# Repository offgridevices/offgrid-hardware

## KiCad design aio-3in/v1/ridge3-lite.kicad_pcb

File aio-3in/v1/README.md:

# Ridge 3 Lite — v1

**One board that does it all:** the flight controller and the 4-in-1 ESC of a
3-inch quad on a single 38 × 38 mm board, for Project Cheap Drone Phase 1. A
battery lead and four motors connect to it, and it flies on stock Betaflight.
It has no FPV parts: no OSD, no video transmitter, no camera connector.

It replaces the GEPRC TAKER G4 AIO that Phase 1 flew. It uses the same
25.5 mm mounting pattern, and Betaflight's own TAKERG4AIO target runs on it
pin for pin.

> **Status: design complete, not yet built.** The board is fully routed
> (`ridge3-lite.kicad_pcb`): KiCad 10 DRC 0 errors, 0 warnings, 0
> unconnected, every fab gate and all 100 checks in `VERIFICATION.md` pass,
> and Gerbers, BOM, CPL and renders are in `production/` and `images/`.
> Nothing has been measured on hardware: build a few and go through
> bring-up before a volume order.

| | |
|---|---|
| Size | 38 × 38 mm, 3 mm corner radius, 25.5 mm M2 holes for soft-mount grommets |
| Battery | 2–4S LiPo, 4S HV (17.4 V) included; XT30 lead on solder pads |
| Motors | 4 × brushless, up to 15 A each continuous, 25 A peak (per-motor current limit) |
| Flight controller | STM32G473CEU6, ICM-42688-P gyro (BMI270 as second source), Betaflight |
| ESCs | 4 × STM32G071 + TI DRV8300D + 6 × Toshiba TPN2R304PL (40 V, 2.3 mΩ), AM32 |
| Power | 5 V 0.6 A BEC (TI LMR36506, 70 V input), 3.3 V for the FC and the ESCs, 11 V gate drive |
| Sensing | battery voltage and current to Betaflight; per-motor current and voltage to each ESC |
| PCB | 8 layers, 1.6 mm, 1 oz copper on every layer, 0.09 mm track and gap, vias down to 0.37 / 0.15 mm, every via filled and capped |

---

## What's on the board

- **Flight controller (top centre).** The STM32G473 runs Betaflight. It has:
  - the gyro on SPI1;
  - an 8 MHz crystal;
  - USB-C with ESD protection;
  - a BOOT button;
  - status and power LEDs;
  - a buzzer switch.

  There is no blackbox flash; log to an OpenLager on UART1 if needed.
- **Four ESCs, one per edge (bottom).** Each motor channel is the same layout,
  turned 90° per edge. Each has:
  - its own STM32G071 running AM32 (stock GEN_64K_G071 target);
  - a DRV8300D gate driver with 22 Ω / 10 Ω gate resistors, chosen by
    simulation to keep the FETs inside 40 V;
  - six FETs;
  - a 0.5 mΩ Kelvin shunt with an INA186 amplifier, so the ESC limits each
    motor's current itself;
  - back-EMF sensing and battery-voltage sensing.
- **Power.**
  - A 70 V-rated buck makes 5 V for the receiver and the LDOs.
  - A 60 V-rated LDO makes the 11 V gate drive.
  - A 22 V TVS clamps spikes on the battery.
  - The board runs from USB alone for configuration: everything powers up
    except the motors.
- **Pads.**
  - Battery + and − at the rear edge.
  - Three motor pads at each edge.
  - The receiver (UART2, 5 V, G) at the front.
  - Aux (UART1, LED strip, buzzer) at the right.
  - USB-C at the left.
  - SWD test points for each ESC's first flash, plated through so a probe
    reaches them from either side.

## Ordering

JLCPCB or PCBWay, from `production/`:

- **8 layers, 1.6 mm, 1 oz copper on every layer.** Layers: F (parts, power) / In1
  ground plane / In2-In4 signals / In5 the channels' return pours / In6 battery plane / B
  (parts, power).
- **0.09 mm (3.5 mil) track and gap, vias down to 0.37 / 0.15 mm** (also 0.4 / 0.2 and 0.5 / 0.25 mm). Both are inside
  JLCPCB's multilayer capability, but they are its fine-line and small-via
  price tiers: expect them on the quote. The board needs them: 260 parts on
  38 mm leave no room for 0.1 mm rules. Going to 40 mm would not help (the
  congestion is round the flight controller in the middle, not at the edges).
- **Matte black solder mask, white silkscreen, ENIG.**
- **Via-in-pad: "Epoxy filled & capped" (POFV).** Every via is filled; on 6+
  layers JLCPCB does this at no extra charge.
- Assembly: upload the BOM and CPL from `production/`. All assembled parts
  are on both sides; JLCPCB's two-sided assembly.
- **Fit by hand after assembly:**
  - the XT30 battery lead on the battery pads;
  - the bulk capacitor across the same pads (`docs/bulk-capacitor.md`:
    2 × Rubycon 35PZK470M10X11, or 1 × Panasonic EEH-AZSV681UB);
  - the motor wires.

**Check before you pay:** the SMF22A-TP's cathode band must face pad 1 (battery
+) in JLCPCB's placement preview. MCC's library symbol does not mark it.

## Bring-up

Firmware and every setting are in `firmware/`, with a README that walks
through it. In short:

1. USB only: flash Betaflight. Use the stock TAKERG4AIO target, or this
   board's RIDGE3LITE build; both are in `firmware/betaflight/`. Then paste
   `cli-setup.txt`.
2. Still on USB: flash each ESC's AM32 bootloader and firmware once over SWD
   (`firmware/am32/flash_esc.sh`). Then set them in ESC-configurator through
   Betaflight passthrough (`esc-settings.md`).
3. Battery, props off:
   - check motor order and direction in Betaflight's Motors tab;
   - check that the gyro moves the right way. The IMU sits at 135°; see
     `firmware/gyro-orientation.md`.

## What was checked

Each check is a gate: the build stops if it fails. All of these pass now.

| Check | Result |
|---|---|
| Every part has a footprint and an LCSC number; every pin is on its footprint; no single-pin net | pass, 260 parts |
| Firmware pin map: FC against Betaflight TAKERG4AIO, all four ESCs against AM32 GEN_64K_G071 (`src/verify.py`) | pass, pin for pin |
| Gyro orientation against Betaflight's alignment maths | pass |
| Routed board, KiCad 10 DRC | 0 errors, 0 warnings, 0 unconnected |
| Every part in production (`docs/lifecycle.md`) | 45 parts checked; 2 swapped for active parts |
| Volume sourcing for 10,000 boards (`docs/sourcing-10k.md`) | second sources and factory lead times listed |

### Simulation (`sim/`)

Worst case: a 4S HV pack (17.4 V), XING2 1404 3800KV on 3" props
(15 A per motor sustained, 25 A stalled).

- **Half-bridge switching (ngspice, fitted FET model).**
  - Peak FET voltage is 29.7–32.2 V at 15 A and 39.4 V at 30 A with 4 nH of
    loop, against the FETs' 40 V. The 22 / 10 Ω gate resistors fixed a
    41–50 V overshoot found in the first draft.
  - The switch node slews at most 1.85 V/ns.
- **Battery spikes.**
  - 18.6 V worst with the bulk capacitor fitted; the TVS never conducts in
    normal use.
  - Unplugging the pack while the motors brake reaches 57 V. No TVS this
    size can absorb that: keep the lead soldered or the XT30 seated.
- **Gate supply, BEC, sense chains.** All within ratings at a 100 °C board.
  The current sense reads 20 mV/A per ESC and 12 mV/A total.
- **Thermal (finite-volume model of the routed eight-layer board; `sim/thermal/`).**
  Validated against Toshiba's published Rth(ch-a) to within 2 %.

### Heat: what the board can do on a hot day

The routed board as ordered (8 layers, 1 oz, bare, no heat sink), 50 °C air,
1000 W/m² of sun on the board, prop wash (`sim/thermal/`, `--case desert`):

| Flight | FET (limit 175) | ESC MCU (105) | Gyro (85) |
|---|---|---|---|
| Armed on the ground, still air | 74 °C | 79 °C | |
| Hover | 98 °C | 95 °C | **89 °C** |
| Cruise | 110 °C | 101 °C | |
| 8 punches of 3 s full throttle | 119 °C | 110 °C | |
| Full throttle, 60 s | 165 °C | **154 °C** | **120 °C** |
| Motor 1 stalled at 25 A for 2 s | **179 °C** | 102 °C | |

At 25 °C in the shade, hover is 67 / 64 / 57 °C and 60 s of full throttle is
130 / 119 / 88 °C.  With half the prop wash, 60 s of full throttle would reach
225 °C: on such a day the ESCs' temperature limit, not the copper, is what
keeps the board alive.  Channel 1 runs hottest: it sits by the battery pads,
where all 60 A enter.  Its FETs are 40 °C above channel 4's at full throttle.

**What this means.**
- In normal flying on a normal day nothing comes near a limit.
- On a 50 °C day in direct sun the board will not burn out. Each ESC's
  temperature limit (AM32, 100 °C on its own chip) throttles that motor back
  first. The ESC chip tracks its FETs closely (154 against 165 °C at the end
  of the 60 s run), so the cut-back starts with the FETs near 110 °C, far
  under their 175 °C. Sustained full throttle on such a day is therefore
  throttled (by about two thirds on the placed board's estimate,
  `sim/thermal/results-size-cooling.md`), more if the prop wash is weak.
- A jammed prop is cut by AM32's stuck-rotor protection; the 2 s stall above
  is the case where it fails to act, and stays within 4 °C of the FET rating.
- Short punches are fine.
- Under those conditions the gyro runs slightly over its rated 85 °C even at
  hover, and Betaflight's gyro drifts with temperature.

**Fixes, in order of value:**
1. Keep the sun off the board. A frame top plate or a canopy over the stack
   removes the 1000 W/m² of sun, the largest single input at hover.
2. A finned aluminium top sink (9.6 g, 4 mm fins) takes 25–35 °C off at full
   throttle.

The full tables, with every cooling option, 35 against 38 mm and 1 against
2 oz, are in `sim/thermal/results-size-cooling.md`.

## Limits

- **Battery:** 2–4S. 5S and up exceed the FETs' 40 V rating under switching
  spikes.
- **The pack must stay connected while the motors spin** (see the 57 V
  case above).
- **Motors:** keep each ESC's current limit at 26 A or lower (`esc-settings.md`).
- **Bulk capacitor:** it must be fitted. Without it the battery ripple is
  2–7 V p-p and a hot plug rings to 26 V.

## Files

```
README.md                  this file
firmware/                  Betaflight and AM32 hex files, settings, flashing scripts
docs/                      lifecycle, 10k sourcing, bulk capacitor, gyro second source
sim/                       circuit simulations (ngspice) and the thermal model
src/                       the generator: circuit, footprints, placement, power copper, routing, checks
tools/                     the pinned KiCad 10 toolchain (Docker) and helpers
```

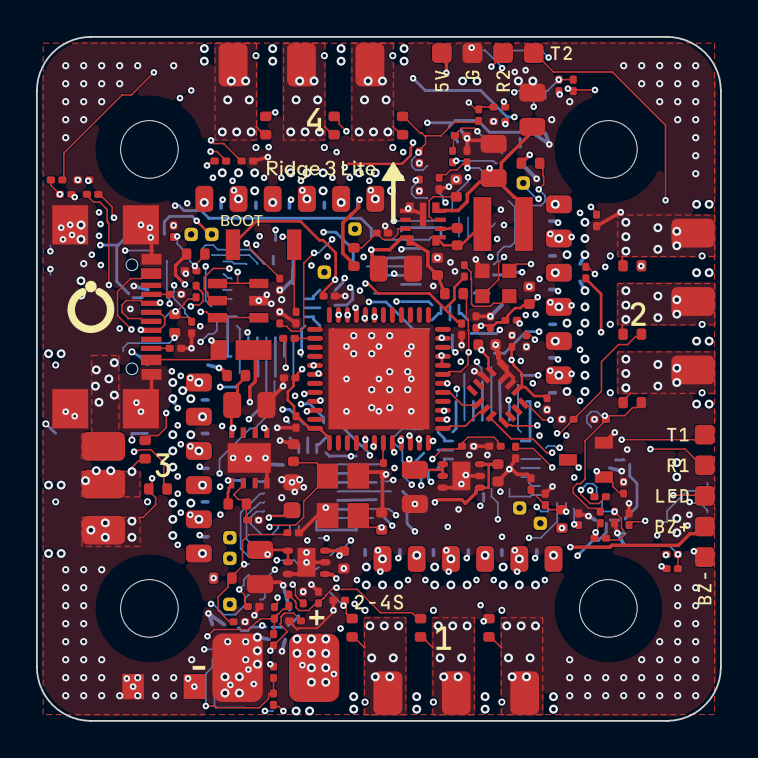
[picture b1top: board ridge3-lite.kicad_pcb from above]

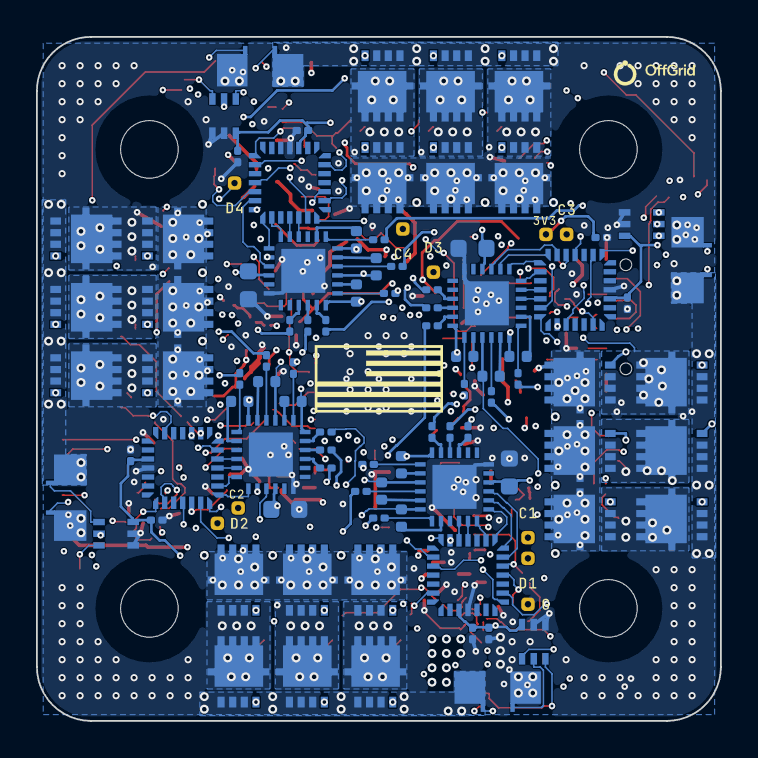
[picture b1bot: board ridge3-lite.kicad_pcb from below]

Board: 8 copper layers, 38.0 x 38.0 mm, 260 parts (88 on the bottom side), 188 nets.

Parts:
C1, C8, C10, C11, C104, C106, C108, C204, C206, C208, C304, C306, C308, C404, C406, C408: 4.7uF; C_0805_2012Metric
C2, C3: 100nF; C_0402_1005Metric_L
C4, C7, C9, C103, C105, C107, C203, C205, C207, C303, C305, C307, C403, C405, C407: 1uF; C_0402_1005Metric_L
C5, C6: 22uF; C_0805_2012Metric
C12, C102, C202, C302, C402: 10uF; C_0603_1608Metric_L
C13, C14, C15, C16, C17, C18, C19, C22, C26, C27, C101, C109, C110, C111, C201, C209, C210, C211, C301, C309, C310, C311, C401, C409, C410, C411: 100nF; C_0201_0603Metric_L
C20: 1uF; C_0201_0603Metric_L
C21, C25: 4.7uF; C_0402_1005Metric_L
C23, C24: 12pF; C_0402_1005Metric_L
D_TVS: SMF22A; SOD-123FL_L2.8-W1.9-LS3.7-RD
D_USB: SS1040HE; SOD-323HE_L2.0-W1.4-LS2.5-RD
H1, H2, H3, H4: HOLE; MOUNT_M2
J_USB: USB-C; USB-C-SMD_TYPE-C-16P-USB4110-GF-A
LED_PWR: red; LED0603-RD
LED_STAT: blue; LED0603-RD
L_BEC: 10uH; IND-SMD_L3.0-W3.0_SWPA3010S
P_5V: PAD_SIG
P_BAT+: PAD_BAT
P_BAT-: PAD_BAT
P_BZ+: PAD_SIG
P_BZ-: PAD_SIG
P_G: PAD_SIG
P_LED: PAD_SIG
P_M1A, P_M1B, P_M1C, P_M2A, P_M2B, P_M2C, P_M3A, P_M3B, P_M3C, P_M4A, P_M4B, P_M4C: PAD_MOTOR
P_R1, P_R2: PAD_SIG
P_T1, P_T2: PAD_SIG
Q1AH, Q1AL, Q1BH, Q1BL, Q1CH, Q1CL, Q2AH, Q2AL, Q2BH, Q2BL, Q2CH, Q2CL, Q3AH, Q3AL, Q3BH, Q3BL, Q3CH, Q3CL, Q4AH, Q4AL, Q4BH, Q4BL, Q4CH, Q4CL: TPN2R304PL; TSON-8_L3.1-W3.1-P0.65-LS3.3-BL-EP
Q_BZ: AO3400A; SOT-23-3_L2.9-W1.3-P1.90-LS2.4-BR
R1, R119, R219, R319, R419: 100k; R_0402_1005Metric_L
R2: 27k; R_0201_0603Metric_L
R3: 10R; R_0402_1005Metric_L
R4: 82k; R_0402_1005Metric_L
R5, R9, R16, R105, R110, R115, R118, R120, R205, R210, R215, R218, R220, R305, R310, R315, R318, R320, R405, R410, R415, R418, R420: 10k; R_0201_0603Metric_L
R6, R103, R108, R113, R203, R208, R213, R303, R308, R313, R403, R408, R413: 10k; R_0402_1005Metric_L
R7, R13, R117, R217, R317, R417: 1k; R_0201_0603Metric_L
R8: 62k; R_0201_0603Metric_L
R10, R102, R107, R112, R202, R207, R212, R302, R307, R312, R402, R407, R412: 10R; R_0201_0603Metric_L
R11, R12: 5.1k; R_0201_0603Metric_L
R14: 330R; R_0201_0603Metric_L
R15: 100R; R_0201_0603Metric_L
R101, R106, R111, R201, R206, R211, R301, R306, R311, R401, R406, R411: 22R; R_0201_0603Metric_L
R104, R109, R114, R204, R209, R214, R304, R309, R314, R404, R409, R414: 2.2k; R_0201_0603Metric_L
R116, R216, R316, R416: 1.5k; R_0201_0603Metric_L
R_S1, R_S2, R_S3, R_S4: 0.5mOhm; RES-SMD_1206_HCS1206
SW_BOOT: BOOT; KEY-SMD_B3U-1000PM
TP_3V3: PAD_TP
TP_C1, TP_C2, TP_C3, TP_C4: PAD_TP
TP_D1, TP_D2, TP_D3, TP_D4: PAD_TP
TP_GND: PAD_TP
U_A1, U_A2, U_A3, U_A4: INA186A3; SC-70-6_L2.0-W1.3-P0.65-LS2.1-BL-1
U_BEC: LMR36506R5; VQFN-9_L2.1-W2.1-P0.50-TL
U_D1, U_D2, U_D3, U_D4: DRV8300DRGER; VQFN-24_L4.0-W4.0-P0.50-TL-EP2.5
U_E1, U_E2, U_E3, U_E4: STM32G071GBU6; UFQFPN-28_L4.0-W4.0-P0.50-BL
U_ESD: USBLC6-2SC6; SOT-23-6_L2.9-W1.6-P0.95-LS2.8-BL
U_FC: STM32G473CEU6; UFQFPN-48_L7.0-W7.0-P0.50-BL-EP5.6
U_GVDD: TPS7A1601; SON-8_L3.0-W3.0-P0.65-TL-EP
U_IMU: ICM-42688-P; LGA-14_L3.0-W2.5-P0.50-TL
U_LDO: TLV76733; WSON-6_L2.0-W2.0-P0.65-TL-EP
U_LDOE: TLV76733; WSON-6_L2.0-W2.0-P0.65-TL-EP
Y1: 8 MHz; CRYSTAL-SMD_4P-L3.2-W2.5-BL

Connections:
+3V3: C8.1, C15.1, C16.1, C17.1, C18.1, C19.1, C20.1, C21.1, R10.1, R13.1, R14.1, SW_BOOT.1, U_FC.1, U_FC.20, U_FC.21, U_FC.23, U_FC.35, U_FC.48, U_LDO.1, U_LDO.2
+3V3E: C10.1, C101.1, C109.1, C201.1, C209.1, C301.1, C309.1, C401.1, C409.1, TP_3V3.1, U_A1.3, U_A2.3, U_A3.3, U_A4.3, U_E1.3, U_E2.3, U_E3.3, U_E4.3, U_LDOE.1, U_LDOE.2
+3V3_GYRO: C25.1, C26.1, C27.1, R10.2, U_IMU.5, U_IMU.8
+5V: C5.1, C6.1, C7.1, C9.1, D_USB.1, L_BEC.2, P_5V.1, P_BZ+.1, U_BEC.8, U_LDO.4, U_LDO.6, U_LDOE.4, U_LDOE.6
ADC_VBAT: C13.1, R6.2, R7.1, U_FC.19
BEC_BOOT: C3.1, U_BEC.6
BEC_EN: R1.2, R2.1, U_BEC.3
BEC_SW: C3.2, L_BEC.1, U_BEC.5
BEC_VCC: C4.1, U_BEC.7
BEEPER: R15.1, U_FC.38
BEEPER_G: Q_BZ.1, R15.2, R16.1
BOOT0: R9.1, SW_BOOT.2, U_FC.46
BZ-: P_BZ-.1, Q_BZ.3
CUR: C14.1, R8.1, R118.2, R218.2, R318.2, R418.2, U_FC.18
GND: C1.2, C2.2, C4.2, C5.2, C6.2, C7.2, C8.2, C9.2, C10.2, C11.2, C12.2, C13.2, C14.2, C15.2, C16.2, C17.2, C18.2, C19.2, C20.2, C21.2, C22.2, C23.2, C24.2, C25.2, C26.2, C27.2, C101.2, C102.2, C109.2, C110.2, C111.2, C201.2, C202.2, C209.2, C210.2, C211.2, C301.2, C302.2, C309.2, C310.2, C311.2, C401.2, C402.2, C409.2, C410.2, C411.2, D_TVS.2, J_USB.8, J_USB.9, J_USB.10, J_USB.11, J_USB.A1B12, J_USB.B1A12, LED_PWR.1, P_BAT-.1, P_G.1, Q_BZ.2, R2.2, R5.2, R7.2, R8.2, R9.2, R11.2, R12.2, R16.2, R104.2, R109.2, R114.2, R117.2, R120.2, R204.2, R209.2, R214.2, R217.2, R220.2, R304.2, R309.2, R314.2, R317.2, R320.2, R404.2, R409.2, R414.2, R417.2, R420.2, R_S1.2, R_S2.2, R_S3.2, R_S4.2, TP_GND.1, U_A1.1, U_A1.2, U_A2.1, U_A2.2, U_A3.1, U_A3.2, U_A4.1, U_A4.2, U_BEC.1, U_BEC.9, U_D1.6, U_D1.25, U_D2.6, U_D2.25, U_D3.6, U_D3.25, U_D4.6, U_D4.25, U_E1.4, U_E2.4, U_E3.4, U_E4.4, U_ESD.2, U_FC.49, U_GVDD.4, U_GVDD.9, U_IMU.6, U_IMU.7, U_IMU.9, U_LDO.3, U_LDO.5, U_LDO.7, U_LDOE.3, U_LDOE.5, U_LDOE.7, Y1.2, Y1.4
GVDD: C12.1, C102.1, C202.1, C302.1, C402.1, R4.1, U_D1.4, U_D2.4, U_D3.4, U_D4.4, U_GVDD.1
GVDD_FB: R4.2, R5.1, U_GVDD.2
GVDD_IN: C11.1, R3.2, U_GVDD.5, U_GVDD.8
GYRO_CS: U_FC.17, U_IMU.12
GYRO_INT: U_FC.12, U_IMU.4
HSE_IN: C23.1, U_FC.5, Y1.1
HSE_OUT: C24.1, U_FC.6, Y1.3
LED0: LED_STAT.1, U_FC.45
LED0_A: LED_STAT.2, R14.2
LED_PWR_A: LED_PWR.2, R13.2
LED_STRIP: P_LED.1, U_FC.44
M1_A: C103.2, P_M1A.1, Q1AH.1, Q1AH.2, Q1AH.3, Q1AL.5, Q1AL.6, Q1AL.7, Q1AL.8, Q1AL.9, R103.1, U_D1.18
M1_B: C105.2, P_M1B.1, Q1BH.1, Q1BH.2, Q1BH.3, Q1BL.5, Q1BL.6, Q1BL.7, Q1BL.8, Q1BL.9, R108.1, U_D1.15
M1_BSTA: C103.1, U_D1.20
M1_BSTB: C105.1, U_D1.17
M1_BSTC: C107.1, U_D1.14
M1_C: C107.2, P_M1C.1, Q1CH.1, Q1CH.2, Q1CH.3, Q1CL.5, Q1CL.6, Q1CL.7, Q1CL.8, Q1CL.9, R113.1, U_D1.12
M1_CMP_A: R103.2, R104.1, R105.1, U_E1.27
M1_CMP_B: R108.2, R109.1, R110.1, U_E1.23
M1_CMP_C: R113.2, R114.1, R115.1, U_E1.8
M1_GHA: Q1AH.4, R101.2
M1_GHA_D: R101.1, U_D1.19
M1_GHB: Q1BH.4, R106.2
M1_GHB_D: R106.1, U_D1.16
M1_GHC: Q1CH.4, R111.2
M1_GHC_D: R111.1, U_D1.13
M1_GLA: Q1AL.4, R102.2
M1_GLA_D: R102.1, U_D1.11
M1_GLB: Q1BL.4, R107.2
M1_GLB_D: R107.1, U_D1.10
M1_GLC: Q1CL.4, R112.2
M1_GLC_D: R112.1, U_D1.9
M1_HA: U_D1.22, U_E1.19
M1_HB: U_D1.23, U_E1.18
M1_HC: U_D1.24, U_E1.16
M1_IOUT: R116.1, R118.1, U_A1.6
M1_ISENSE: C110.1, R116.2, R117.1, U_E1.11
M1_LA: U_D1.1, U_E1.15
M1_LB: U_D1.2, U_E1.14
M1_LC: U_D1.3, U_E1.13
M1_NEUTRAL: R105.2, R110.2, R115.2, U_E1.9
M1_SIG: U_E1.24, U_FC.8
M1_SNSN: R_S1.4, U_A1.5
M1_SNSP: R_S1.3, U_A1.4
M1_SRC: C104.2, C106.2, C108.2, Q1AL.1, Q1AL.2, Q1AL.3, Q1BL.1, Q1BL.2, Q1BL.3, Q1CL.1, Q1CL.2, Q1CL.3, R_S1.1
M1_SWCLK: TP_C1.1, U_E1.21
M1_SWDIO: TP_D1.1, U_E1.20
M1_VSENSE: C111.1, R119.2, R120.1, U_E1.12
M2_A: C203.2, P_M2A.1, Q2AH.1, Q2AH.2, Q2AH.3, Q2AL.5, Q2AL.6, Q2AL.7, Q2AL.8, Q2AL.9, R203.1, U_D2.18
M2_B: C205.2, P_M2B.1, Q2BH.1, Q2BH.2, Q2BH.3, Q2BL.5, Q2BL.6, Q2BL.7, Q2BL.8, Q2BL.9, R208.1, U_D2.15
M2_BSTA: C203.1, U_D2.20
M2_BSTB: C205.1, U_D2.17
M2_BSTC: C207.1, U_D2.14
M2_C: C207.2, P_M2C.1, Q2CH.1, Q2CH.2, Q2CH.3, Q2CL.5, Q2CL.6, Q2CL.7, Q2CL.8, Q2CL.9, R213.1, U_D2.12
M2_CMP_A: R203.2, R204.1, R205.1, U_E2.27
M2_CMP_B: R208.2, R209.1, R210.1, U_E2.23
M2_CMP_C: R213.2, R214.1, R215.1, U_E2.8
M2_GHA: Q2AH.4, R201.2
M2_GHA_D: R201.1, U_D2.19
M2_GHB: Q2BH.4, R206.2
M2_GHB_D: R206.1, U_D2.16
M2_GHC: Q2CH.4, R211.2
M2_GHC_D: R211.1, U_D2.13
M2_GLA: Q2AL.4, R202.2
M2_GLA_D: R202.1, U_D2.11
M2_GLB: Q2BL.4, R207.2
M2_GLB_D: R207.1, U_D2.10
M2_GLC: Q2CL.4, R212.2
M2_GLC_D: R212.1, U_D2.9
M2_HA: U_D2.22, U_E2.19
M2_HB: U_D2.23, U_E2.18
M2_HC: U_D2.24, U_E2.16
M2_IOUT: R216.1, R218.1, U_A2.6
M2_ISENSE: C210.1, R216.2, R217.1, U_E2.11
M2_LA: U_D2.1, U_E2.15
M2_LB: U_D2.2, U_E2.14
M2_LC: U_D2.3, U_E2.13
M2_NEUTRAL: R205.2, R210.2, R215.2, U_E2.9
M2_SIG: U_E2.24, U_FC.9
M2_SNSN: R_S2.4, U_A2.5
M2_SNSP: R_S2.3, U_A2.4
M2_SRC: C204.2, C206.2, C208.2, Q2AL.1, Q2AL.2, Q2AL.3, Q2BL.1, Q2BL.2, Q2BL.3, Q2CL.1, Q2CL.2, Q2CL.3, R_S2.1
M2_SWCLK: TP_C2.1, U_E2.21
M2_SWDIO: TP_D2.1, U_E2.20
M2_VSENSE: C211.1, R219.2, R220.1, U_E2.12
M3_A: C303.2, P_M3A.1, Q3AH.1, Q3AH.2, Q3AH.3, Q3AL.5, Q3AL.6, Q3AL.7, Q3AL.8, Q3AL.9, R303.1, U_D3.18
M3_B: C305.2, P_M3B.1, Q3BH.1, Q3BH.2, Q3BH.3, Q3BL.5, Q3BL.6, Q3BL.7, Q3BL.8, Q3BL.9, R308.1, U_D3.15
M3_BSTA: C303.1, U_D3.20
M3_BSTB: C305.1, U_D3.17
M3_BSTC: C307.1, U_D3.14
M3_C: C307.2, P_M3C.1, Q3CH.1, Q3CH.2, Q3CH.3, Q3CL.5, Q3CL.6, Q3CL.7, Q3CL.8, Q3CL.9, R313.1, U_D3.12
M3_CMP_A: R303.2, R304.1, R305.1, U_E3.27
M3_CMP_B: R308.2, R309.1, R310.1, U_E3.23
M3_CMP_C: R313.2, R314.1, R315.1, U_E3.8
M3_GHA: Q3AH.4, R301.2
M3_GHA_D: R301.1, U_D3.19
M3_GHB: Q3BH.4, R306.2
M3_GHB_D: R306.1, U_D3.16
M3_GHC: Q3CH.4, R311.2
M3_GHC_D: R311.1, U_D3.13
M3_GLA: Q3AL.4, R302.2
M3_GLA_D: R302.1, U_D3.11
M3_GLB: Q3BL.4, R307.2
M3_GLB_D: R307.1, U_D3.10
M3_GLC: Q3CL.4, R312.2
M3_GLC_D: R312.1, U_D3.9
M3_HA: U_D3.22, U_E3.19
M3_HB: U_D3.23, U_E3.18
M3_HC: U_D3.24, U_E3.16
M3_IOUT: R316.1, R318.1, U_A3.6
M3_ISENSE: C310.1, R316.2, R317.1, U_E3.11
M3_LA: U_D3.1, U_E3.15
M3_LB: U_D3.2, U_E3.14
M3_LC: U_D3.3, U_E3.13
M3_NEUTRAL: R305.2, R310.2, R315.2, U_E3.9
M3_SIG: U_E3.24, U_FC.10
M3_SNSN: R_S3.4, U_A3.5
M3_SNSP: R_S3.3, U_A3.4
M3_SRC: C304.2, C306.2, C308.2, Q3AL.1, Q3AL.2, Q3AL.3, Q3BL.1, Q3BL.2, Q3BL.3, Q3CL.1, Q3CL.2, Q3CL.3, R_S3.1
M3_SWCLK: TP_C3.1, U_E3.21
M3_SWDIO: TP_D3.1, U_E3.20
M3_VSENSE: C311.1, R319.2, R320.1, U_E3.12
M4_A: C403.2, P_M4A.1, Q4AH.1, Q4AH.2, Q4AH.3, Q4AL.5, Q4AL.6, Q4AL.7, Q4AL.8, Q4AL.9, R403.1, U_D4.18
M4_B: C405.2, P_M4B.1, Q4BH.1, Q4BH.2, Q4BH.3, Q4BL.5, Q4BL.6, Q4BL.7, Q4BL.8, Q4BL.9, R408.1, U_D4.15
M4_BSTA: C403.1, U_D4.20
M4_BSTB: C405.1, U_D4.17
M4_BSTC: C407.1, U_D4.14
M4_C: C407.2, P_M4C.1, Q4CH.1, Q4CH.2, Q4CH.3, Q4CL.5, Q4CL.6, Q4CL.7, Q4CL.8, Q4CL.9, R413.1, U_D4.12
M4_CMP_A: R403.2, R404.1, R405.1, U_E4.27
M4_CMP_B: R408.2, R409.1, R410.1, U_E4.23
M4_CMP_C: R413.2, R414.1, R415.1, U_E4.8
M4_GHA: Q4AH.4, R401.2
M4_GHA_D: R401.1, U_D4.19
M4_GHB: Q4BH.4, R406.2
M4_GHB_D: R406.1, U_D4.16
M4_GHC: Q4CH.4, R411.2
M4_GHC_D: R411.1, U_D4.13
M4_GLA: Q4AL.4, R402.2
M4_GLA_D: R402.1, U_D4.11
M4_GLB: Q4BL.4, R407.2
M4_GLB_D: R407.1, U_D4.10
M4_GLC: Q4CL.4, R412.2
M4_GLC_D: R412.1, U_D4.9
M4_HA: U_D4.22, U_E4.19
M4_HB: U_D4.23, U_E4.18
M4_HC: U_D4.24, U_E4.16
M4_IOUT: R416.1, R418.1, U_A4.6
M4_ISENSE: C410.1, R416.2, R417.1, U_E4.11
M4_LA: U_D4.1, U_E4.15
M4_LB: U_D4.2, U_E4.14
M4_LC: U_D4.3, U_E4.13
M4_NEUTRAL: R405.2, R410.2, R415.2, U_E4.9
M4_SIG: U_E4.24, U_FC.11
M4_SNSN: R_S4.4, U_A4.5
M4_SNSP: R_S4.3, U_A4.4
M4_SRC: C404.2, C406.2, C408.2, Q4AL.1, Q4AL.2, Q4AL.3, Q4BL.1, Q4BL.2, Q4BL.3, Q4CL.1, Q4CL.2, Q4CL.3, R_S4.1
M4_SWCLK: TP_C4.1, U_E4.21
M4_SWDIO: TP_D4.1, U_E4.20
M4_VSENSE: C411.1, R419.2, R420.1, U_E4.12
NRST: C22.1, U_FC.7
SPI1_MISO: U_FC.14, U_IMU.1
SPI1_MOSI: U_FC.15, U_IMU.14
SPI1_SCK: U_FC.13, U_IMU.13
UART1_RX: P_R1.1, U_FC.32
UART1_TX: P_T1.1, U_FC.31
UART2_RX: P_R2.1, U_FC.42
UART2_TX: P_T2.1, U_FC.41
USB_CC1: J_USB.A5, R11.1
USB_CC2: J_USB.B5, R12.1
USB_DM: J_USB.A7, J_USB.B7, U_ESD.3, U_ESD.4, U_FC.33
USB_DP: J_USB.A6, J_USB.B6, U_ESD.1, U_ESD.6, U_FC.34
USB_VBUS: D_USB.2, J_USB.A4B9, J_USB.B4A9, U_ESD.5
VBAT: C1.1, C2.1, C104.1, C106.1, C108.1, C204.1, C206.1, C208.1, C304.1, C306.1, C308.1, C404.1, C406.1, C408.1, D_TVS.1, P_BAT+.1, Q1AH.5, Q1AH.6, Q1AH.7, Q1AH.8, Q1AH.9, Q1BH.5, Q1BH.6, Q1BH.7, Q1BH.8, Q1BH.9, Q1CH.5, Q1CH.6, Q1CH.7, Q1CH.8, Q1CH.9, Q2AH.5, Q2AH.6, Q2AH.7, Q2AH.8, Q2AH.9, Q2BH.5, Q2BH.6, Q2BH.7, Q2BH.8, Q2BH.9, Q2CH.5, Q2CH.6, Q2CH.7, Q2CH.8, Q2CH.9, Q3AH.5, Q3AH.6, Q3AH.7, Q3AH.8, Q3AH.9, Q3BH.5, Q3BH.6, Q3BH.7, Q3BH.8, Q3BH.9, Q3CH.5, Q3CH.6, Q3CH.7, Q3CH.8, Q3CH.9, Q4AH.5, Q4AH.6, Q4AH.7, Q4AH.8, Q4AH.9, Q4BH.5, Q4BH.6, Q4BH.7, Q4BH.8, Q4BH.9, Q4CH.5, Q4CH.6, Q4CH.7, Q4CH.8, Q4CH.9, R1.1, R3.1, R6.1, R119.1, R219.1, R319.1, R419.1, U_BEC.4

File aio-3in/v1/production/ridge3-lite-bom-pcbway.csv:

Item #,Designator,Qty,Manufacturer Part Number,Description,Value,Package/Footprint,Type,LCSC Part #,Side
1,"R5,R9,R16,R105,R110,R115,R118,R120,R205,R210,R215,R218,R220,R305,R310,R315,R318,R320,R405,R410,R415,R418,R420",23,RC0201FR-0710KL,Resistor 10k 1% 0201,10k,R_0201_0603Metric_L,SMD,C106225,Top
2,"R10,R102,R107,R112,R202,R207,R212,R302,R307,R312,R402,R407,R412",13,RC0201FR-0710RL,Resistor 10R 1% 0201,10R,R_0201_0603Metric_L,SMD,C106226,Bottom+Top
3,LED_PWR,1,LTST-C191KRKT,LED red 0603 (pad 1 cathode),red,LED0603-RD,SMD,C125099,Top
4,U_FC,1,STM32G473CEU6,"MCU Cortex-M4F 170 MHz, 512 KB flash, UFQFPN-48 (flight controller)",STM32G473CEU6,UFQFPN-48_L7.0-W7.0-P0.50-BL-EP5.6,SMD,C1342773,Top
5,"R7,R13,R117,R217,R317,R417",6,RC0201FR-071KL,Resistor 1k 1% 0201,1k,R_0201_0603Metric_L,SMD,C138165,Top
6,"R104,R109,R114,R204,R209,R214,R304,R309,R314,R404,R409,R414",12,RC0201FR-072K2L,Resistor 2.2k 1% 0201,2.2k,R_0201_0603Metric_L,SMD,C142018,Top
7,"C23,C24",2,0402CG120J500NT,Capacitor 12pF 50V C0G 0402,12pF,C_0402_1005Metric_L,SMD,C1547,Top
8,"R101,R106,R111,R201,R206,R211,R301,R306,R311,R401,R406,R411",12,RC0201FR-0722RL,Resistor 22R 1% 0201,22R,R_0201_0603Metric_L,SMD,C155743,Bottom
9,"C8,C10",2,CL21A475KAQNNNE,Capacitor 4.7uF 25V X5R 0805,4.7uF,C_0805_2012Metric,SMD,C1779,Top
10,U_IMU,1,ICM-42688-P,"6-axis IMU (gyro + accelerometer), SPI, LGA-14 2.5 x 3",ICM-42688-P,LGA-14_L3.0-W2.5-P0.50-TL,SMD,C1850418,Top
11,D_TVS,1,SMF22A-TP,"TVS 22 V stand-off, 35.5 V clamp at 5.6 A, 200 W, SOD-123FL",SMF22A,SOD-123FL_L2.8-W1.9-LS3.7-RD,SMD,C1974299,Top
12,"U_A1,U_A2,U_A3,U_A4",4,INA186A3IDCKR,"Current-sense amplifier 100 V/V, zero drift, SC-70-6",INA186A3,SC-70-6_L2.0-W1.3-P0.65-LS2.1-BL-1,SMD,C2058245,Bottom
13,Q_BZ,1,AO3400A,"N-MOSFET 30 V 5.7 A, SOT-23 (buzzer)",AO3400A,SOT-23-3_L2.9-W1.3-P1.90-LS2.4-BR,SMD,C20917,Top
14,SW_BOOT,1,B3U-1000P,Tactile switch 3 x 2.5 mm (DFU boot),BOOT,KEY-SMD_B3U-1000PM,SMD,C231329,Top
15,"C21,C25",2,CL05A475MP5NRNC,Capacitor 4.7uF 10V X5R 0402,4.7uF,C_0402_1005Metric_L,SMD,C23733,Top
16,R3,1,0402WGF100JTCE,Resistor 10R 1% 0402,10R,R_0402_1005Metric_L,SMD,C25077,Top
17,"R1,R119,R219,R319,R419",5,0402WGF1003TCE,Resistor 100k 1% 0402,100k,R_0402_1005Metric_L,SMD,C25741,Top
18,"R6,R103,R108,R113,R203,R208,R213,R303,R308,R313,R403,R408,R413",13,0402WGF1002TCE,Resistor 10k 1% 0402,10k,R_0402_1005Metric_L,SMD,C25744,Top
19,"R116,R216,R316,R416",4,0201WMF1501TEE,Resistor 1.5k 1% 0201,1.5k,R_0201_0603Metric_L,SMD,C270361,Top
20,R2,1,RC0201FR-0727KL,Resistor 27k 1% 0201,27k,R_0201_0603Metric_L,SMD,C273283,Top
21,"R11,R12",2,RC0201FR-075K1L,Resistor 5.1k 1% 0201,5.1k,R_0201_0603Metric_L,SMD,C274341,Top
22,R14,1,RC0201FR-07330RL,Resistor 330R 1% 0201,330R,R_0201_0603Metric_L,SMD,C274872,Top
23,D_USB,1,SS1040HEWS_R1_00001,"Schottky 40 V 1 A, SOD-323HE (USB OR-ing)",SS1040HE,SOD-323HE_L2.0-W1.4-LS2.5-RD,SMD,C282389,Top
24,"U_LDO,U_LDOE",2,TLV76733DRVR,"LDO 3.3 V 1 A, 16 V in, WSON-6 2 x 2",TLV76733,WSON-6_L2.0-W2.0-P0.65-TL-EP,SMD,C2848334,Top
25,U_BEC,1,LMR36506R5RPER,"Buck 4.2-65 V in, fixed 5 V 0.6 A, VQFN-HR-9 2 x 2 (BEC)",LMR36506R5,VQFN-9_L2.1-W2.1-P0.50-TL,SMD,C2866484,Top
26,U_GVDD,1,TPS7A1601DRBR,"LDO adjustable 100 mA, 60 V in, SON-8 3 x 3 (gate-drive supply)",TPS7A1601,SON-8_L3.0-W3.0-P0.65-TL-EP,SMD,C2867753,Top
27,R8,1,RC0201FR-0762KL,Resistor 62k 1% 0201,62k,R_0201_0603Metric_L,SMD,C295812,Top
28,"C2,C3",2,CL05B104KB54PNC,Capacitor 100nF 50V X7R 0402,100nF,C_0402_1005Metric_L,SMD,C307331,Top
29,"C13,C14,C15,C16,C17,C18,C19,C22,C26,C27,C101,C109,C110,C111,C201,C209,C210,C211,C301,C309,C310,C311,C401,C409,C410,C411",26,CL03A104KO3NNNC,Capacitor 100nF 16V X5R 0201,100nF,C_0201_0603Metric_L,SMD,C307380,Bottom+Top
30,"R_S1,R_S2,R_S3,R_S4",4,HCS1206FTL500,"Current shunt 0.5 mOhm 1 % 2 W, metal element, 1206",0.5mOhm,RES-SMD_1206_HCS1206,SMD,C346511,Bottom
31,"U_D1,U_D2,U_D3,U_D4",4,DRV8300DRGER,"100 V three-phase gate driver, bootstrap diodes, VQFN-24 4 x 4",DRV8300DRGER,VQFN-24_L4.0-W4.0-P0.50-TL-EP2.5,SMD,C3655801,Bottom
32,"C1,C11,C104,C106,C108,C204,C206,C208,C304,C306,C308,C404,C406,C408",14,GRM21BZ71H475KE15L,Capacitor 4.7uF 50V X7R 0805,4.7uF,C_0805_2012Metric,SMD,C437557,Top
33,L_BEC,1,SWPA3015S100MT,"Inductor 10 uH, 0.92 A sat, 0.77 A rms, 325 mOhm, shielded 3 x 3 x 1.5",10uH,IND-SMD_L3.0-W3.0_SWPA3010S,SMD,C45403,Top
34,R4,1,CRCW040282K0FKED,Resistor 82k 1% 0402,82k,R_0402_1005Metric_L,SMD,C482240,Top
35,J_USB,1,USB4110-GF-A,"USB-C receptacle, USB 2.0, 16 contacts, all-SMD shell",USB-C,USB-C-SMD_TYPE-C-16P-USB4110-GF-A,SMD,C5143397,Top
36,"C4,C7,C9,C103,C105,C107,C203,C205,C207,C303,C305,C307,C403,C405,C407",15,CL05A105KA5NQNC,Capacitor 1uF 25V X5R 0402,1uF,C_0402_1005Metric_L,SMD,C52923,Bottom+Top
37,"U_E1,U_E2,U_E3,U_E4",4,STM32G071GBU6,"MCU Cortex-M0+ 64 MHz, 128 KB flash, UFQFPN-28 (ESC, AM32)",STM32G071GBU6,UFQFPN-28_L4.0-W4.0-P0.50-BL,SMD,C529347,Bottom
38,Y1,1,ECS-80-10-33-CHN-TR3,"Crystal 8 MHz 10 ppm, 10 pF, 3.2 x 2.5",8 MHz,CRYSTAL-SMD_4P-L3.2-W2.5-BL,SMD,C5727434,Top
39,"Q1AH,Q1AL,Q1BH,Q1BL,Q1CH,Q1CL,Q2AH,Q2AL,Q2BH,Q2BL,Q2CH,Q2CL,Q3AH,Q3AL,Q3BH,Q3BL,Q3CH,Q3CL,Q4AH,Q4AL,Q4BH,Q4BL,Q4CH,Q4CL",24,"TPN2R304PL,L1Q","N-MOSFET 40 V 80 A, 2.3 mOhm max at 10 V, TSON Advance 3.3 x 3.3",TPN2R304PL,TSON-8_L3.1-W3.1-P0.65-LS3.3-BL-EP,SMD,C5802634,Bottom
40,U_ESD,1,USBLC6-2SC6,"USB ESD protection, SOT-23-6",USBLC6-2SC6,SOT-23-6_L2.9-W1.6-P0.95-LS2.8-BL,SMD,C7519,Top
41,C20,1,GRM033R61A105ME44D,Capacitor 1uF 10V X5R 0201,1uF,C_0201_0603Metric_L,SMD,C76935,Top
42,R15,1,RC0201FR-07100RL,Resistor 100R 1% 0201,100R,R_0201_0603Metric_L,SMD,C77623,Top
43,"C5,C6",2,GRM21BR61E226ME44L,Capacitor 22uF 25V X5R 0805,22uF,C_0805_2012Metric,SMD,C86816,Top
44,"C12,C102,C202,C302,C402",5,CL10A106MA8NRNC,Capacitor 10uF 25V X5R 0603,10uF,C_0603_1608Metric_L,SMD,C96446,Bottom+Top
45,LED_STAT,1,LTST-C191TBKT,LED blue 0603 (pad 1 cathode),blue,LED0603-RD,SMD,C99290,Top

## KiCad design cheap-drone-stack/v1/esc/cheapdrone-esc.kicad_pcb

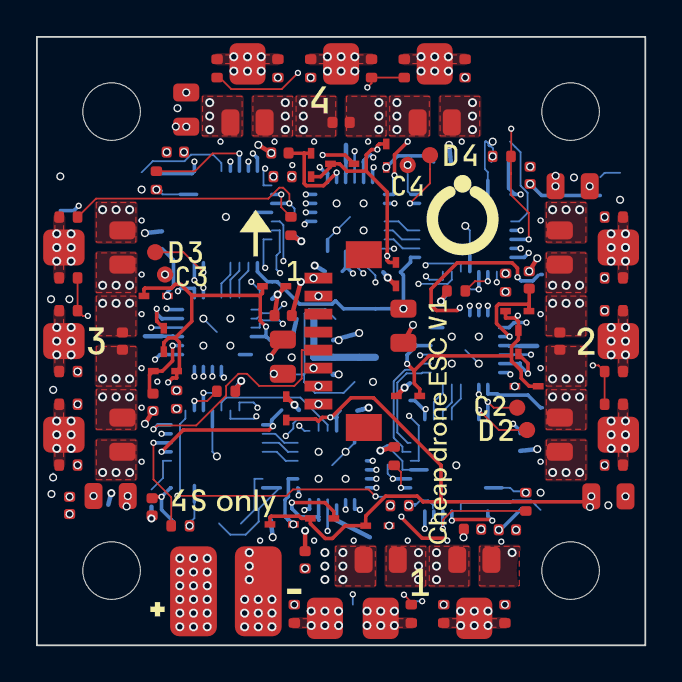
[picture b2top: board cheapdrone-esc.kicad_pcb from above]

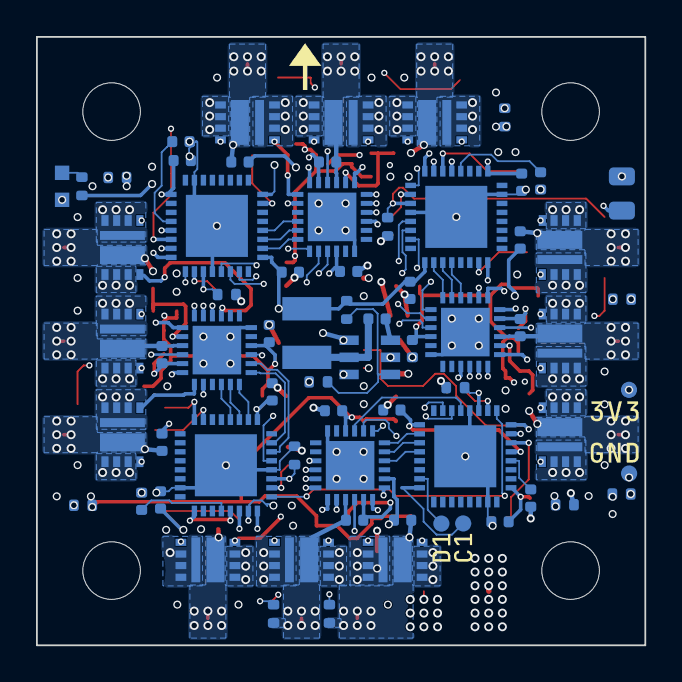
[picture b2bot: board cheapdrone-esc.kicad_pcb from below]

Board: 6 copper layers, 33.8 x 33.8 mm, 171 parts (68 on the bottom side), 116 nets.

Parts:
C1, C11, C16, C17, C23, C28, C29, C35, C40, C41, C47, C52, C53: 10uF; C_0805_2012Metric
C2, C3, C6, C7, C10, C12, C18, C19, C22, C24, C30, C31, C34, C36, C42, C43, C46, C48, C54: 100nF; C_0402_1005Metric
C4, C5: 22uF; C_0805_2012Metric
C8, C20, C32, C44: 4.7uF; C_0402_1005Metric
C9, C13, C14, C15, C21, C25, C26, C27, C33, C37, C38, C39, C45, C49, C50, C51: 1uF; C_0402_1005Metric
D1, D5, D9, D13: 15V; SOD-523_L1.2-W0.8-LS1.6-RD
D2, D3, D4, D6, D7, D8, D10, D11, D12, D14, D15, D16: RB521S30; SOD-523_L1.2-W0.8-LS1.6-RD
H1, H2, H3, H4: HOLE; HOLE_M3
J_FC: SH-8P V; CONN-TH_BM08B-SRSS-TB-LF-SN
L1: 4.7uH; IND-SMD_L3.0-W3.0_FNR30XXS
LED_PWR: RED; LED-SMD_L1.6-W0.8-R-RD
P_BAT+: PAD_BAT
P_BAT-: PAD_BAT
P_M1A, P_M1B, P_M1C, P_M2A, P_M2B, P_M2C, P_M3A, P_M3B, P_M3C, P_M4A, P_M4B, P_M4C: PAD_MOTOR
Q1A, Q1B, Q1C, Q2A, Q2B, Q2C, Q3A, Q3B, Q3C, Q4A, Q4B, Q4C: AON7934; DFN-8_L3.0-W3.0-P0.65-BL_AON7934
R1: 100k; R_0402_1005Metric
R2: 22k; R_0402_1005Metric
R3: 1k; R_0402_1005Metric
R4: 11k; R_0402_1005Metric
R5: 2k; R_0402_1005Metric
R6, R17, R28, R39: 330R; R_0402_1005Metric
R7, R9, R10, R12, R13, R15, R18, R20, R21, R23, R24, R26, R29, R31, R32, R34, R35, R37, R40, R42, R43, R45, R46, R48: 10k; R_0402_1005Metric
R8, R11, R14, R19, R22, R25, R30, R33, R36, R41, R44, R47: 2.2k; R_0402_1005Metric
R16, R27, R38, R49: 750R; R_0402_1005Metric
TP_3V3: PAD_TP
TP_E1_CLK, TP_E1_DIO, TP_E2_CLK, TP_E2_DIO, TP_E3_CLK, TP_E3_DIO, TP_E4_CLK, TP_E4_DIO: PAD_TP
TP_GND: PAD_TP
U_BUCK: LMR51420YDDCR; SOT-23-6_L2.9-W1.6-P0.95-LS2.9-BL
U_ESC1, U_ESC2, U_ESC3, U_ESC4: STM32F051K6U6; UFQFPN-32_L5.0-W5.0-P0.50-BL-EP
U_GD1, U_GD2, U_GD3, U_GD4: JSM6288Q; VQFN-24_L4.0-W4.0-P0.50-TL-EP2.7

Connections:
+3V3: C4.1, C5.1, C7.1, C8.1, C9.1, C19.1, C20.1, C21.1, C31.1, C32.1, C33.1, C43.1, C44.1, C45.1, L1.2, R1.1, R3.1, TP_3V3.1, U_ESC1.1, U_ESC1.5, U_ESC1.17, U_ESC2.1, U_ESC2.5, U_ESC2.17, U_ESC3.1, U_ESC3.5, U_ESC3.17, U_ESC4.1, U_ESC4.5, U_ESC4.17
BUCK_CB: C3.1, U_BUCK.6
BUCK_FB: R1.2, R2.1, U_BUCK.4
BUCK_SW: C3.2, L1.1, U_BUCK.2
ESC_VSENSE: C6.1, R4.2, R5.1, U_ESC1.9, U_ESC2.9, U_ESC3.9, U_ESC4.9
GND: C1.2, C2.2, C4.2, C5.2, C6.2, C7.2, C8.2, C9.2, C10.2, C11.2, C12.2, C16.2, C17.2, C18.2, C19.2, C20.2, C21.2, C22.2, C23.2, C24.2, C28.2, C29.2, C30.2, C31.2, C32.2, C33.2, C34.2, C35.2, C36.2, C40.2, C41.2, C42.2, C43.2, C44.2, C45.2, C46.2, C47.2, C48.2, C52.2, C53.2, C54.2, D1.2, D5.2, D9.2, D13.2, J_FC.2, LED_PWR.2, P_BAT-.1, Q1A.5, Q1A.6, Q1A.7, Q1B.5, Q1B.6, Q1B.7, Q1C.5, Q1C.6, Q1C.7, Q2A.5, Q2A.6, Q2A.7, Q2B.5, Q2B.6, Q2B.7, Q2C.5, Q2C.6, Q2C.7, Q3A.5, Q3A.6, Q3A.7, Q3B.5, Q3B.6, Q3B.7, Q3C.5, Q3C.6, Q3C.7, Q4A.5, Q4A.6, Q4A.7, Q4B.5, Q4B.6, Q4B.7, Q4C.5, Q4C.6, Q4C.7, R2.2, R5.2, R8.2, R11.2, R14.2, R16.2, R19.2, R22.2, R25.2, R27.2, R30.2, R33.2, R36.2, R38.2, R41.2, R44.2, R47.2, R49.2, TP_GND.1, U_BUCK.1, U_ESC1.12, U_ESC1.31, U_ESC1.33, U_ESC2.12, U_ESC2.31, U_ESC2.33, U_ESC3.12, U_ESC3.31, U_ESC3.33, U_ESC4.12, U_ESC4.31, U_ESC4.33, U_GD1.6, U_GD1.25, U_GD2.6, U_GD2.25, U_GD3.6, U_GD3.25, U_GD4.6, U_GD4.25
LED_PWR_A: LED_PWR.1, R3.2
M1_A: C13.2, P_M1A.1, Q1A.10, R7.1, R9.1, U_GD1.18
M1_B: C14.2, P_M1B.1, Q1B.10, R10.1, R12.1, U_GD1.15
M1_C: C15.2, P_M1C.1, Q1C.10, R13.1, R15.1, U_GD1.12
M1_CMP_A: R7.2, R8.1, U_ESC1.11
M1_CMP_B: R10.2, R11.1, U_ESC1.10
M1_CMP_C: R13.2, R14.1, U_ESC1.6
M1_GHA: Q1A.1, U_GD1.19
M1_GHB: Q1B.1, U_GD1.16
M1_GHC: Q1C.1, U_GD1.13
M1_GLA: Q1A.8, U_GD1.11
M1_GLB: Q1B.8, U_GD1.10
M1_GLC: Q1C.8, U_GD1.9
M1_HA: U_ESC1.20, U_GD1.22
M1_HB: U_ESC1.19, U_GD1.23
M1_HC: U_ESC1.18, U_GD1.24
M1_LA: U_ESC1.15, U_GD1.1
M1_LB: U_ESC1.14, U_GD1.2
M1_LC: U_ESC1.13, U_GD1.3
M1_NEUTRAL: R9.2, R12.2, R15.2, R16.1, U_ESC1.7
M1_NRST: C10.1, U_ESC1.4
M1_SIG: J_FC.5, U_ESC1.8
M1_SWCLK: TP_E1_CLK.1, U_ESC1.24
M1_SWDIO: TP_E1_DIO.1, U_ESC1.23
M1_VBA: C13.1, D2.1, U_GD1.20
M1_VBB: C14.1, D3.1, U_GD1.17
M1_VBC: C15.1, D4.1, U_GD1.14
M1_VCC: C11.1, C12.1, D1.1, D2.2, D3.2, D4.2, R6.2, U_GD1.4
M2_A: C25.2, P_M2A.1, Q2A.10, R18.1, R20.1, U_GD2.18
M2_B: C26.2, P_M2B.1, Q2B.10, R21.1, R23.1, U_GD2.15
M2_C: C27.2, P_M2C.1, Q2C.10, R24.1, R26.1, U_GD2.12
M2_CMP_A: R18.2, R19.1, U_ESC2.11
M2_CMP_B: R21.2, R22.1, U_ESC2.10
M2_CMP_C: R24.2, R25.1, U_ESC2.6
M2_GHA: Q2A.1, U_GD2.19
M2_GHB: Q2B.1, U_GD2.16
M2_GHC: Q2C.1, U_GD2.13
M2_GLA: Q2A.8, U_GD2.11
M2_GLB: Q2B.8, U_GD2.10
M2_GLC: Q2C.8, U_GD2.9
M2_HA: U_ESC2.20, U_GD2.22
M2_HB: U_ESC2.19, U_GD2.23
M2_HC: U_ESC2.18, U_GD2.24
M2_LA: U_ESC2.15, U_GD2.1
M2_LB: U_ESC2.14, U_GD2.2
M2_LC: U_ESC2.13, U_GD2.3
M2_NEUTRAL: R20.2, R23.2, R26.2, R27.1, U_ESC2.7
M2_NRST: C22.1, U_ESC2.4
M2_SIG: J_FC.6, U_ESC2.8
M2_SWCLK: TP_E2_CLK.1, U_ESC2.24
M2_SWDIO: TP_E2_DIO.1, U_ESC2.23
M2_VBA: C25.1, D6.1, U_GD2.20
M2_VBB: C26.1, D7.1, U_GD2.17
M2_VBC: C27.1, D8.1, U_GD2.14
M2_VCC: C23.1, C24.1, D5.1, D6.2, D7.2, D8.2, R17.2, U_GD2.4
M3_A: C37.2, P_M3A.1, Q3A.10, R29.1, R31.1, U_GD3.18
M3_B: C38.2, P_M3B.1, Q3B.10, R32.1, R34.1, U_GD3.15
M3_C: C39.2, P_M3C.1, Q3C.10, R35.1, R37.1, U_GD3.12
M3_CMP_A: R29.2, R30.1, U_ESC3.11
M3_CMP_B: R32.2, R33.1, U_ESC3.10
M3_CMP_C: R35.2, R36.1, U_ESC3.6
M3_GHA: Q3A.1, U_GD3.19
M3_GHB: Q3B.1, U_GD3.16
M3_GHC: Q3C.1, U_GD3.13
M3_GLA: Q3A.8, U_GD3.11
M3_GLB: Q3B.8, U_GD3.10
M3_GLC: Q3C.8, U_GD3.9
M3_HA: U_ESC3.20, U_GD3.22
M3_HB: U_ESC3.19, U_GD3.23
M3_HC: U_ESC3.18, U_GD3.24
M3_LA: U_ESC3.15, U_GD3.1
M3_LB: U_ESC3.14, U_GD3.2
M3_LC: U_ESC3.13, U_GD3.3
M3_NEUTRAL: R31.2, R34.2, R37.2, R38.1, U_ESC3.7
M3_NRST: C34.1, U_ESC3.4
M3_SIG: J_FC.7, U_ESC3.8
M3_SWCLK: TP_E3_CLK.1, U_ESC3.24
M3_SWDIO: TP_E3_DIO.1, U_ESC3.23
M3_VBA: C37.1, D10.1, U_GD3.20
M3_VBB: C38.1, D11.1, U_GD3.17
M3_VBC: C39.1, D12.1, U_GD3.14
M3_VCC: C35.1, C36.1, D9.1, D10.2, D11.2, D12.2, R28.2, U_GD3.4
M4_A: C49.2, P_M4A.1, Q4A.10, R40.1, R42.1, U_GD4.18
M4_B: C50.2, P_M4B.1, Q4B.10, R43.1, R45.1, U_GD4.15
M4_C: C51.2, P_M4C.1, Q4C.10, R46.1, R48.1, U_GD4.12
M4_CMP_A: R40.2, R41.1, U_ESC4.11
M4_CMP_B: R43.2, R44.1, U_ESC4.10
M4_CMP_C: R46.2, R47.1, U_ESC4.6
M4_GHA: Q4A.1, U_GD4.19
M4_GHB: Q4B.1, U_GD4.16
M4_GHC: Q4C.1, U_GD4.13
M4_GLA: Q4A.8, U_GD4.11
M4_GLB: Q4B.8, U_GD4.10
M4_GLC: Q4C.8, U_GD4.9
M4_HA: U_ESC4.20, U_GD4.22
M4_HB: U_ESC4.19, U_GD4.23
M4_HC: U_ESC4.18, U_GD4.24
M4_LA: U_ESC4.15, U_GD4.1
M4_LB: U_ESC4.14, U_GD4.2
M4_LC: U_ESC4.13, U_GD4.3
M4_NEUTRAL: R42.2, R45.2, R48.2, R49.1, U_ESC4.7
M4_NRST: C46.1, U_ESC4.4
M4_SIG: J_FC.8, U_ESC4.8
M4_SWCLK: TP_E4_CLK.1, U_ESC4.24
M4_SWDIO: TP_E4_DIO.1, U_ESC4.23
M4_VBA: C49.1, D14.1, U_GD4.20
M4_VBB: C50.1, D15.1, U_GD4.17
M4_VBC: C51.1, D16.1, U_GD4.14
M4_VCC: C47.1, C48.1, D13.1, D14.2, D15.2, D16.2, R39.2, U_GD4.4
VBAT: C1.1, C2.1, C16.1, C17.1, C18.1, C28.1, C29.1, C30.1, C40.1, C41.1, C42.1, C52.1, C53.1, C54.1, J_FC.1, P_BAT+.1, Q1A.2, Q1A.3, Q1A.4, Q1A.9, Q1B.2, Q1B.3, Q1B.4, Q1B.9, Q1C.2, Q1C.3, Q1C.4, Q1C.9, Q2A.2, Q2A.3, Q2A.4, Q2A.9, Q2B.2, Q2B.3, Q2B.4, Q2B.9, Q2C.2, Q2C.3, Q2C.4, Q2C.9, Q3A.2, Q3A.3, Q3A.4, Q3A.9, Q3B.2, Q3B.3, Q3B.4, Q3B.9, Q3C.2, Q3C.3, Q3C.4, Q3C.9, Q4A.2, Q4A.3, Q4A.4, Q4A.9, Q4B.2, Q4B.3, Q4B.4, Q4B.9, Q4C.2, Q4C.3, Q4C.4, Q4C.9, R4.1, R6.1, R17.1, R28.1, R39.1, U_BUCK.3, U_BUCK.5

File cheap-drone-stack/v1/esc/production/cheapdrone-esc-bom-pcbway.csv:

Item #,Designator,Qty,Manufacturer Part Number,Description,Value,Package/Footprint,Type,LCSC Part #,Side
1,R3,1,0402WGF1001TCE,Resistor 1k 1% 0402,1k,R_0402_1005Metric,SMD,C11702,Bottom
2,J_FC,1,BM08B-SRSS-TB(LF)(SN),JST SH 8-pin vertical SMD,SH-8P V,CONN-TH_BM08B-SRSS-TB-LF-SN,SMD,C160394,Top
3,L1,1,FNR3015S4R7MT,Inductor 4.7 uH 1.3 A shielded 3x3,4.7uH,IND-SMD_L3.0-W3.0_FNR30XXS,SMD,C167753,Bottom
4,"U_GD1,U_GD2,U_GD3,U_GD4",4,JSM6288Q,"3-phase gate driver (FD6288Q equiv.), QFN-24 4x4",JSM6288Q,VQFN-24_L4.0-W4.0-P0.50-TL-EP2.7,SMD,C19077370,Bottom
5,LED_PWR,1,KT-0603R,LED red 0603 (basic),RED,LED-SMD_L1.6-W0.8-R-RD,SMD,C2286,Bottom
6,"C8,C20,C32,C44",4,CL05A475MP5NRNC,Capacitor 4.7uF 10V X5R 0402,4.7uF,C_0402_1005Metric,SMD,C23733,Bottom
7,"R6,R17,R28,R39",4,0402WGF3300TCE,Resistor 330R 1% 0402,330R,R_0402_1005Metric,SMD,C25104,Bottom
8,"R16,R27,R38,R49",4,0402WGF7500TCE,Resistor 750R 1% 0402,750R,R_0402_1005Metric,SMD,C25132,Top
9,R1,1,0402WGF1003TCE,Resistor 100k 1% 0402,100k,R_0402_1005Metric,SMD,C25741,Bottom
10,"R7,R9,R10,R12,R13,R15,R18,R20,R21,R23,R24,R26,R29,R31,R32,R34,R35,R37,R40,R42,R43,R45,R46,R48",24,0402WGF1002TCE,Resistor 10k 1% 0402,10k,R_0402_1005Metric,SMD,C25744,Bottom+Top
11,R4,1,0402WGF1102TCE,Resistor 11k 1% 0402,11k,R_0402_1005Metric,SMD,C25749,Bottom
12,R2,1,0402WGF2202TCE,Resistor 22k 1% 0402,22k,R_0402_1005Metric,SMD,C25768,Bottom
13,"R8,R11,R14,R19,R22,R25,R30,R33,R36,R41,R44,R47",12,0402WGF2201TCE,Resistor 2.2k 1% 0402,2.2k,R_0402_1005Metric,SMD,C25879,Bottom+Top
14,"C1,C11,C16,C17,C23,C28,C29,C35,C40,C41,C47,C52,C53",13,CL21A106KBYQNNE,Capacitor 10uF 50V X5R 0805,10uF,C_0805_2012Metric,SMD,C2932476,Top
15,"C2,C3,C6,C7,C10,C12,C18,C19,C22,C24,C30,C31,C34,C36,C42,C43,C46,C48,C54",19,CL05B104KB54PNC,Capacitor 100nF 50V X7R 0402,100nF,C_0402_1005Metric,SMD,C307331,Bottom+Top
16,R5,1,0402WGF2001TCE,Resistor 2k 1% 0402,2k,R_0402_1005Metric,SMD,C4109,Bottom
17,"C4,C5",2,CL21A226MAQNNNE,Capacitor 22uF 25V X5R 0805,22uF,C_0805_2012Metric,SMD,C45783,Bottom+Top
18,"Q1A,Q1B,Q1C,Q2A,Q2B,Q2C,Q3A,Q3B,Q3C,Q4A,Q4B,Q4C",12,AON7934,"Dual asymmetric N-MOSFET half-bridge 30 V, DFN3x3",AON7934,DFN-8_L3.0-W3.0-P0.65-BL_AON7934,SMD,C485677,Bottom
19,"C9,C13,C14,C15,C21,C25,C26,C27,C33,C37,C38,C39,C45,C49,C50,C51",16,CL05A105KA5NQNC,Capacitor 1uF 25V X5R 0402,1uF,C_0402_1005Metric,SMD,C52923,Bottom+Top
20,U_BUCK,1,LMR51420YDDCR,"Buck 4.5-36 V in, 2 A, 1.1 MHz, SOT-23-6",LMR51420YDDCR,SOT-23-6_L2.9-W1.6-P0.95-LS2.9-BL,SMD,C5383002,Bottom
21,"D1,D5,D9,D13",4,"BZX585-C15,135","Zener 15 V 300 mW, SOD-523",15V,SOD-523_L1.2-W0.8-LS1.6-RD,SMD,C550633,Top
22,"U_ESC1,U_ESC2,U_ESC3,U_ESC4",4,STM32F051K6U6,"ESC MCU Cortex-M0 48 MHz, UFQFPN-32",STM32F051K6U6,UFQFPN-32_L5.0-W5.0-P0.50-BL-EP,SMD,C81451,Bottom
23,"D2,D3,D4,D6,D7,D8,D10,D11,D12,D14,D15,D16",12,RB521S-30,"Schottky 30 V 200 mA, SOD-523 (JSCJ; alt. onsemi RB521S30T1G C145179)",RB521S30,SOD-523_L1.2-W0.8-LS1.6-RD,SMD,C8523,Top
